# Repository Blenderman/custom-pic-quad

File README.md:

# custom-pic-quad
= Introduction =

This project is about building Microchip PIC-based (PIC24EP512GP806) flight control board and respective software from the board design to the flight. 
All the code is developed from scratch with no third-party libraries and other "black-boxes". 

I am working on completely independent (not a port of existing autopilots) quadrocopter firmware for Microchip PIC24 microprocessors.
The project includes full source code of all the libraries (I2C, UART, ADC, RC Receiver) written from the ground up to be interrupt-based, 
which allowed to implement control loop that can operate at up to 500 Hz.

My quad is flying and I am planning to concentrate now on additions to the project to include more sensors like ultrasonic range finder, 
GPS, barometer as well as testing new RC components like RC receivers with the UART output.

= Details =

If you are interested in this project and would like to see more details about the board that I am working on, the SW presented here, and the project overall, please check my blog http://flightcontroller.blogspot.com/.

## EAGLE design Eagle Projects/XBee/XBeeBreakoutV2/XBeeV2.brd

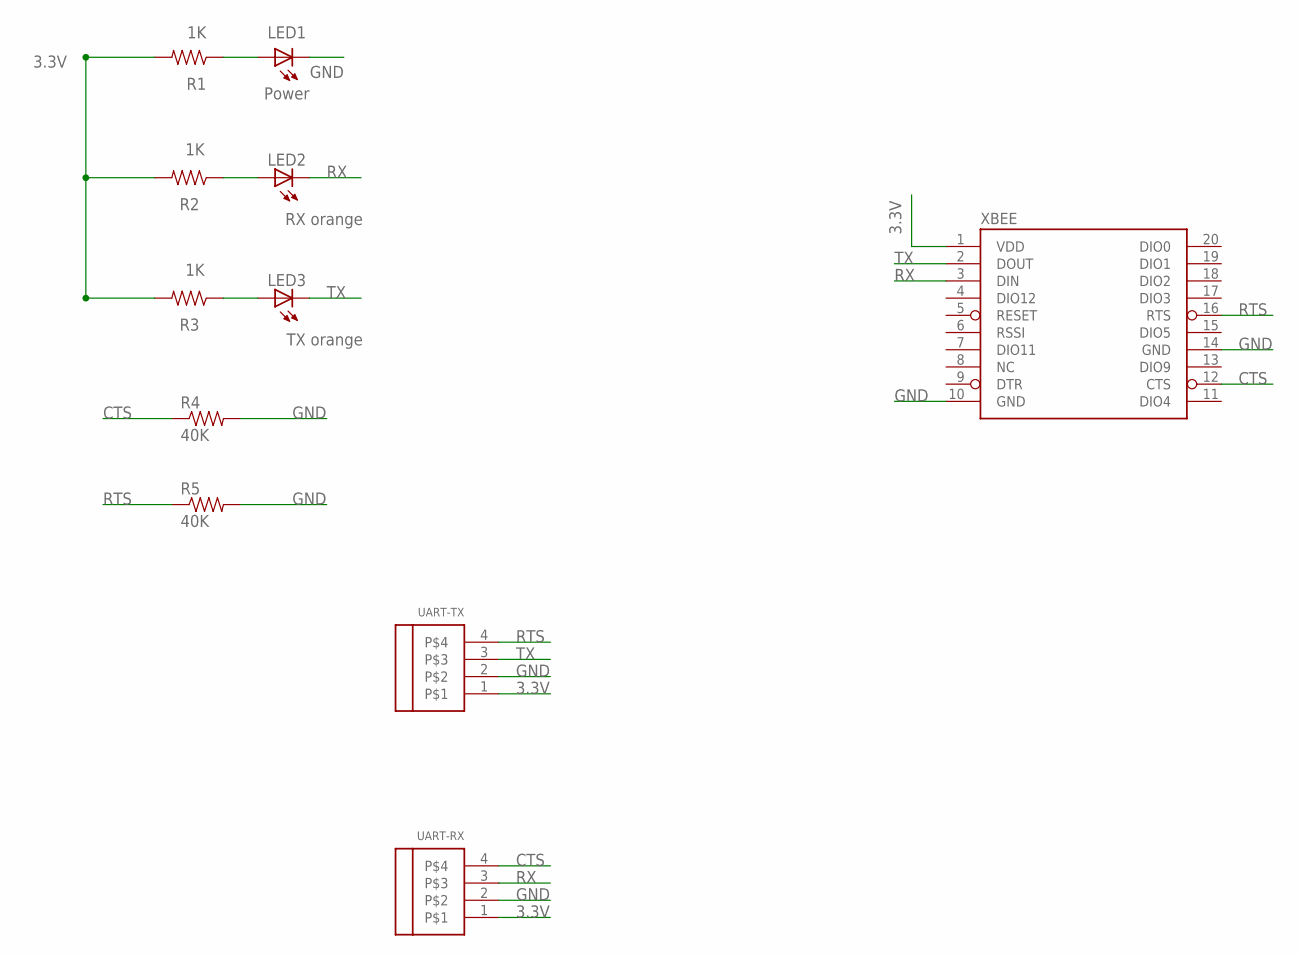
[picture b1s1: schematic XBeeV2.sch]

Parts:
LED1: Power; 1206_INCH-HS-LED
LED2: RX orange; 1206_INCH-HS-LED
LED3: TX orange; 1206_INCH-HS-LED
R1, R2, R3: 1K; 0805_INCH-HS
R4, R5: 40K; 0805_INCH-HS
UART-RX: HEADER-04_JST-ZH_JST-ZH; 1X04-JST-ZH
UART-TX: HEADER-04_JST-ZH_JST-ZH; 1X04-JST-ZH
XBEE: XBEELOCK-SMALL-PRINT; XBEE-1_LOCK

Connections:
3.3V: R1.2, R2.2, R3.2, UART-RX.1, UART-TX.1, XBEE.1 (VDD)
CTS: R4.1, UART-RX.4, XBEE.12 (CTS)
GND: LED1.C, R4.2, R5.2, UART-RX.2, UART-TX.2, XBEE.10 (GND), XBEE.14 (GND)
unnamed: LED3.A, R3.1
unnamed: LED2.A, R2.1
unnamed: LED1.A, R1.1
RTS: R5.1, UART-TX.4, XBEE.16 (RTS)
RX: LED2.C, UART-RX.3, XBEE.3 (DIN)
TX: LED3.C, UART-TX.3, XBEE.2 (DOUT)

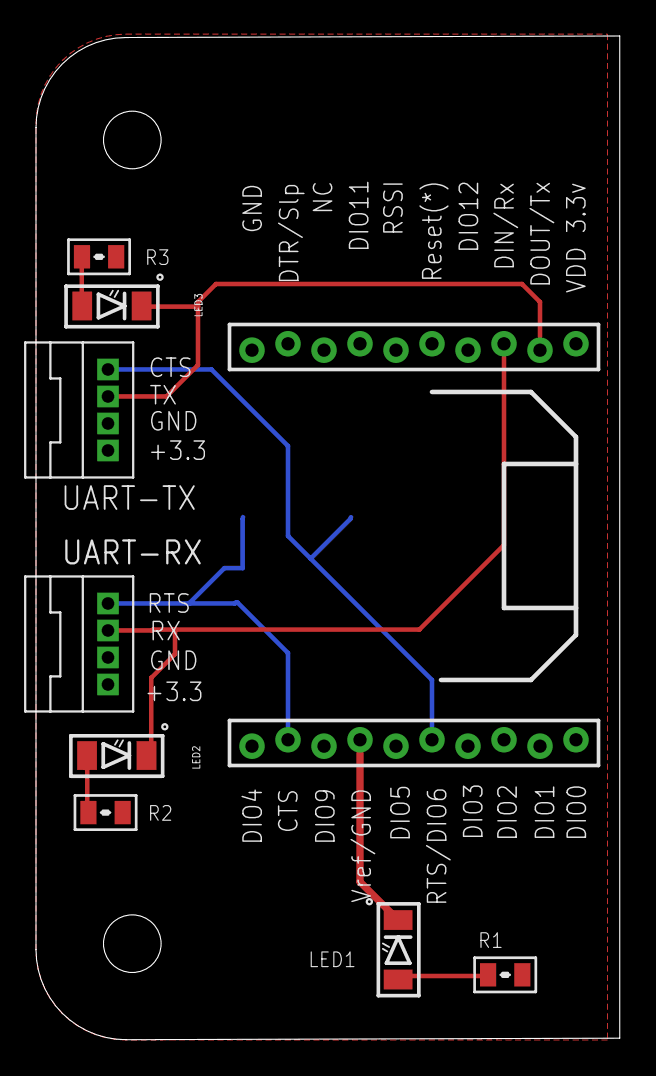
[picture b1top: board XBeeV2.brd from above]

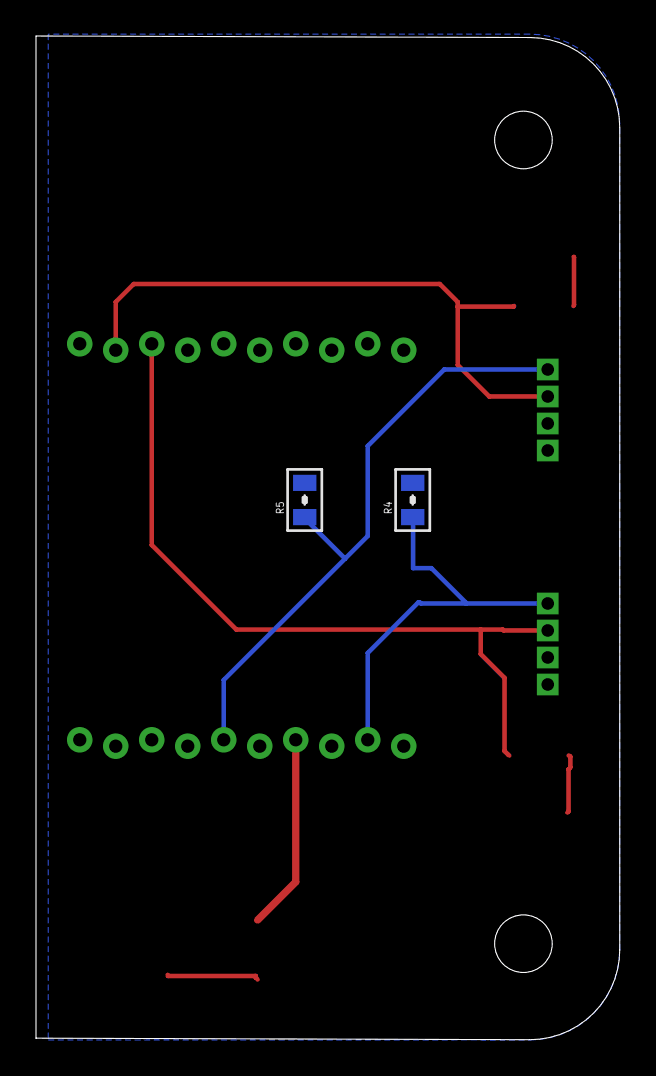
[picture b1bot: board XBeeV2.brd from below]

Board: 2 copper layers, 32.4 x 55.8 mm, 11 parts (2 on the bottom side), 9 nets.

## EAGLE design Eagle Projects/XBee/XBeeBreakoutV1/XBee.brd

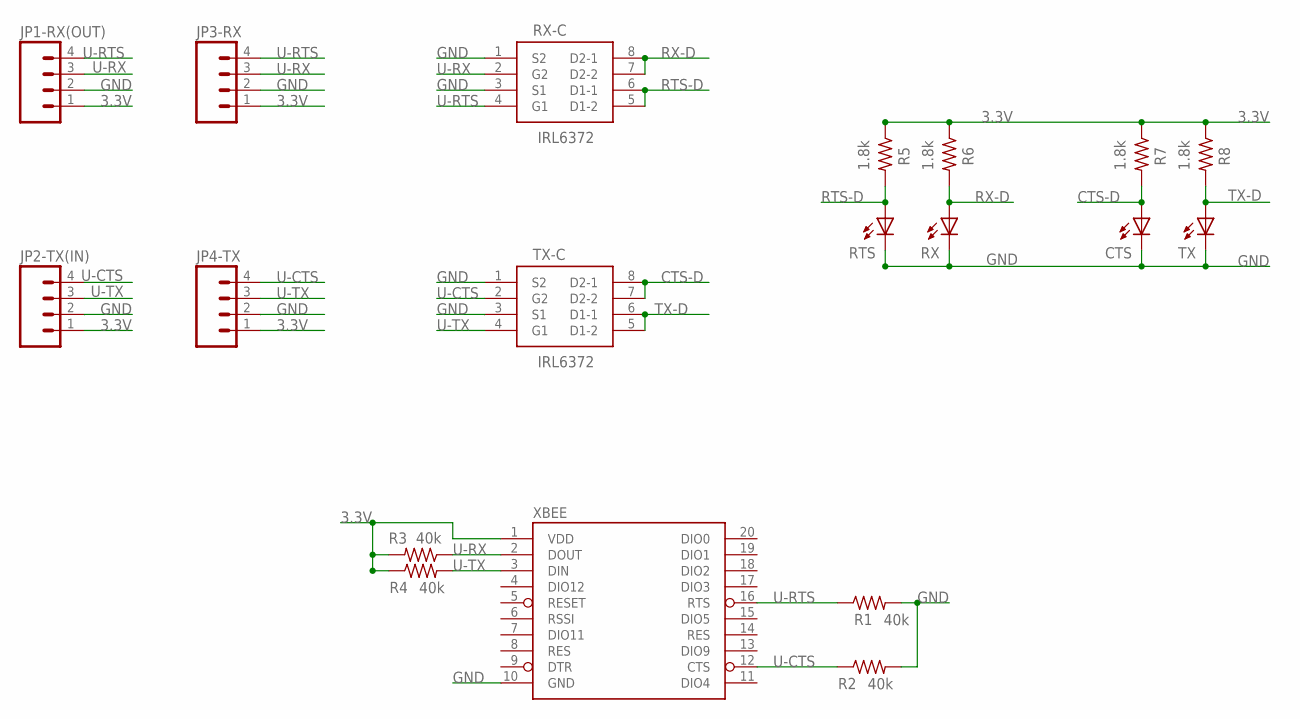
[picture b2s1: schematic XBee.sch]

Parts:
CTS: LED3MM
JP1-RX(OUT), JP2-TX(IN), JP3-RX, JP4-TX: M04LOCK_LONGPADS; 1X04_LOCK_LONGPADS
R1, R2, R3, R4: 40k; 0204/7
R5, R6, R7, R8: 1.8k; 0204/7
RTS: LED3MM
RX: LED3MM
RX-C: IRL6372; SO08-LARGE-PAD-AZ
TX: LED3MM
TX-C: IRL6372; SO08-LARGE-PAD-AZ
XBEE: XBEELOCK-SMALL-PRINT; XBEE-1_LOCK

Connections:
3.3V: JP1-RX(OUT).1, JP2-TX(IN).1, JP3-RX.1, JP4-TX.1, R3.2, R4.1, R5.1, R6.1, R7.1, R8.1, XBEE.1 (VDD)
CTS-D: CTS.A, R7.2, TX-C.7 (D2-2), TX-C.8 (D2-1)
GND: CTS.K (C), JP1-RX(OUT).2, JP2-TX(IN).2, JP3-RX.2, JP4-TX.2, R1.2, R2.2, RTS.K (C), RX.K (C), RX-C.1 (S2), RX-C.3 (S1), TX.K (C), TX-C.1 (S2), TX-C.3 (S1), XBEE.10 (GND)
RTS-D: R5.2, RTS.A, RX-C.5 (D1-2), RX-C.6 (D1-1)
RX-D: R6.2, RX.A, RX-C.7 (D2-2), RX-C.8 (D2-1)
TX-D: R8.2, TX.A, TX-C.5 (D1-2), TX-C.6 (D1-1)
U-CTS: JP2-TX(IN).4, JP4-TX.4, R2.1, TX-C.2 (G2), XBEE.12 (CTS)
U-RTS: JP1-RX(OUT).4, JP3-RX.4, R1.1, RX-C.4 (G1), XBEE.16 (RTS)
U-RX: JP1-RX(OUT).3, JP3-RX.3, R3.1, RX-C.2 (G2), XBEE.2 (DOUT)
U-TX: JP2-TX(IN).3, JP4-TX.3, R4.2, TX-C.4 (G1), XBEE.3 (DIN)

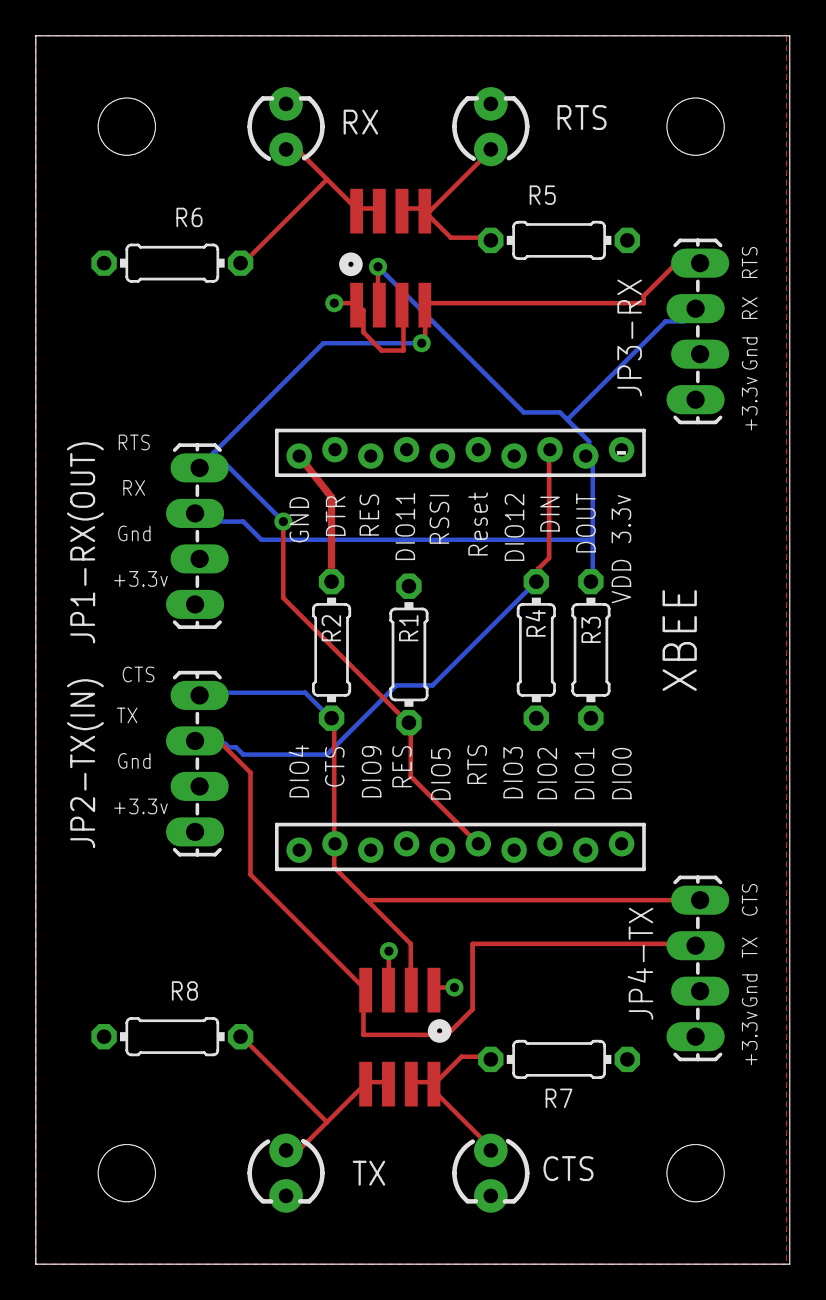
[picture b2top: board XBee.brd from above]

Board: 2 copper layers, 42.1 x 68.6 mm, 19 parts (0 on the bottom side), 10 nets.

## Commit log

2015-03-13 Migrating wiki contents from Google Code
2015-03-14 Initial update
    Initial update after migrating off Google Code
2015-03-14 Some ReadMe updates
2015-03-14 Updated .gitignore
2015-03-15 GIT files
2015-03-15 Before merge
2015-03-15 Removing from SYNC unnecessary directories
2015-03-15 Test
2015-03-15 removing unnecessary files, updating .gitignore
2015-03-15 Test Commit
2015-03-15 Clean-up
2015-03-15 Replacing "\" for "/" in <include> statements
2015-03-15 Another gitignore :)
2015-03-15 Yet another gitignore update :)
2015-03-17 Added Eagle projects
    Added Eagle projects for Quad control boards V2 and V3, as well as
    projects for Data Logger and XBee breakout board. Updated gitignore to
    include ignores related to Eagle.
2015-03-17 Updated gitignore to include additional MPLab-X files/directories
2015-03-17 Removed MPLab-X generated files as per latest gitignore
2015-03-29 Updated code for LogStreamer and LogConverter
    Updated code for LogStreamer and LogConverter to match respective
    projects in the Quad-support section
2015-04-14 Some cosmetic clean-up of I2C library and related components
2015-05-02 Cleaning up spaces and tabs
2015-05-03 Some clean-up of MPL library
2015-05-03 Cleaning up some MPL_Sync.c logic
2015-05-03 Adding/revising some comments
2015-05-04 Updating 14-MPLI2C-Sync poroject
2015-05-13 Updating comments and some code clean-up
    Updating comments and some code clean-up as related to asynchronous
    functions of the MPL Library.
2015-05-15 Some updates/simplifications
2015-05-15 Preparing 15-MPLI2C-Async for blog post
2015-06-17 Further code updates
    Primarily clean-up and some updates for MPU-6050
2015-06-23 ADC Library update and related Init(...) changes
2015-07-05 Basic re-sync after computer rebuild
2015-07-15 Projects cleaned-up from leftovers of SVN
    <<<<<<HEAD and >>>>>Master that slipped into code were removed
2015-07-26 Recent updates, some new libraries
2015-07-26 Correcting invalid upload

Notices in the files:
parts and their libraries:
SparkFun-Connectors: Licensing: CC v3.0 Share-Alike You are welcome to use this library for commercial purposes.
